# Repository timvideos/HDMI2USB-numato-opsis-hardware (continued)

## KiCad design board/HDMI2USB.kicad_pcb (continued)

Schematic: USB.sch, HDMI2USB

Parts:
C34, C35, C37, C38, C39, C40, C41, C42, C240: 0.1uFD
C43, C44, C52, C53, C54, C58, C66, C201, C202: 0.1MFD
C62, C64: 12pF
D2: LED
GS2: GS2
J1, J7: USB_MICRO_B
P11, P12, P13: CONN_1
P16, P17: CONN_5
P18: CONN_2
R13: 8.06K
R14, R23, R24, R26: 100R
R15, R27, R28: 330R
R30: 20K5%- 0.05W
R31: 1.5K
R32, R35, R36: 10K
R33, R34: 2.2K
R37: 4.7K
U2: CY7C68013A_100AC
U18: USB3340
U24: BDXXGA5WEFJ_
X1: CRYSTAL

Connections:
/FPGA_Bank_1_2/CY-IFCLK: U2.26 (*IFCLK); also elsewhere on the board
/FPGA_Bank_1_2/CYPRESS-RESET: U2.77 (RESET#); also elsewhere on the board
/FPGA_Bank_1_2/CY_CTL0: U2.54 (CTL0/FLAGA); also elsewhere on the board
/FPGA_Bank_1_2/CY_CTL1: U2.55 (CTL1/FLAGB); also elsewhere on the board
/FPGA_Bank_1_2/CY_CTL2: U2.56 (CTL2/FLAGC); also elsewhere on the board
/FPGA_Bank_1_2/CY_CTL3: U2.51 (CTL3); also elsewhere on the board
/FPGA_Bank_1_2/CY_CTL4: U2.52 (CTL4); also elsewhere on the board
/FPGA_Bank_1_2/CY_CTL5: U2.76 (CTL5); also elsewhere on the board
/FPGA_Bank_1_2/CY_FD0: U2.34 (PB0/FD0); also elsewhere on the board
/FPGA_Bank_1_2/CY_FD1: U2.35 (PB1/FD1); also elsewhere on the board
/FPGA_Bank_1_2/CY_FD2: U2.36 (PB2/FD2); also elsewhere on the board
/FPGA_Bank_1_2/CY_FD3: U2.37 (PB3/FD3); also elsewhere on the board
/FPGA_Bank_1_2/CY_FD4: U2.44 (PB4/FD4); also elsewhere on the board
/FPGA_Bank_1_2/CY_FD5: U2.45 (PB5/FD5); also elsewhere on the board
/FPGA_Bank_1_2/CY_FD6: U2.46 (PB6/FD6); also elsewhere on the board
/FPGA_Bank_1_2/CY_FD7: U2.47 (PB7/FD7); also elsewhere on the board
/FPGA_Bank_1_2/CY_FD8: U2.80 (PD0/FD8); also elsewhere on the board
/FPGA_Bank_1_2/CY_FD9: U2.81 (PD1/FD9); also elsewhere on the board
/FPGA_Bank_1_2/CY_FD10: U2.82 (PD2/FD10); also elsewhere on the board
/FPGA_Bank_1_2/CY_FD11: U2.83 (PD3/FD11); also elsewhere on the board
/FPGA_Bank_1_2/CY_FD12: U2.95 (PD4/FD12); also elsewhere on the board
/FPGA_Bank_1_2/CY_FD13: U2.96 (PD5/FD13); also elsewhere on the board
/FPGA_Bank_1_2/CY_FD14: U2.97 (PD6/FD14); also elsewhere on the board
/FPGA_Bank_1_2/CY_FD15: U2.98 (PD7/FD15); also elsewhere on the board
/FPGA_Bank_1_2/CY_INT5: U2.84 (INIT5#); also elsewhere on the board
/FPGA_Bank_1_2/CY_PA0: U2.67 (PA0/INT0#); also elsewhere on the board
/FPGA_Bank_1_2/CY_PA1: U2.68 (PA1/INT1#); also elsewhere on the board
/FPGA_Bank_1_2/CY_PA2: U2.69 (PA2/*SLOE); also elsewhere on the board
/FPGA_Bank_1_2/CY_PA3: U2.70 (PA3/*WU2); also elsewhere on the board
/FPGA_Bank_1_2/CY_PA4: U2.71 (PA4/FIFOADR0); also elsewhere on the board
/FPGA_Bank_1_2/CY_PA5: U2.72 (PA5/FIFOADR1); also elsewhere on the board
/FPGA_Bank_1_2/CY_PA6: U2.73 (PA6/*PKTEND); also elsewhere on the board
/FPGA_Bank_1_2/CY_PA7: U2.74 (PA7/*FLAGD/SLCS#); also elsewhere on the board
/FPGA_Bank_1_2/CY_PC0: U2.57 (PC0/GPIFADR0); also elsewhere on the board
/FPGA_Bank_1_2/CY_PC1: U2.58 (PC1/GPIFADR1); also elsewhere on the board
/FPGA_Bank_1_2/CY_PC2: U2.59 (PC2/GPIFADR2); also elsewhere on the board
/FPGA_Bank_1_2/CY_PC3: U2.60 (PC3/GPIFADR3); also elsewhere on the board
/FPGA_Bank_1_2/CY_PC4: U2.61 (PC4/GPIFADR4); also elsewhere on the board
/FPGA_Bank_1_2/CY_PC5: U2.62 (PC5/GPIFADR5); also elsewhere on the board
/FPGA_Bank_1_2/CY_PC6: U2.63 (PC6/GPIFADR6); also elsewhere on the board
/FPGA_Bank_1_2/CY_PC7: U2.64 (PC7/GPIFADR7); also elsewhere on the board
/FPGA_Bank_1_2/CY_RD: U2.31 (RD#); also elsewhere on the board
/FPGA_Bank_1_2/CY_RD0: U2.3 (RDY0/SLRD); also elsewhere on the board
/FPGA_Bank_1_2/CY_RD1: U2.4 (RDY1/SLWR); also elsewhere on the board
/FPGA_Bank_1_2/CY_RD2: U2.5 (RDY2); also elsewhere on the board
/FPGA_Bank_1_2/CY_RD3: U2.6 (RDY3); also elsewhere on the board
/FPGA_Bank_1_2/CY_RD4: U2.7 (RDY4); also elsewhere on the board
/FPGA_Bank_1_2/CY_RD5: U2.8 (RDY5); also elsewhere on the board
/FPGA_Bank_1_2/CY_RXD0: U2.43 (RXD1); also elsewhere on the board
/FPGA_Bank_1_2/CY_RXD1: U2.41 (RXD0); also elsewhere on the board
/FPGA_Bank_1_2/CY_T0: U2.23 (T0); also elsewhere on the board
/FPGA_Bank_1_2/CY_TXD0: U2.42 (TXD1); also elsewhere on the board
/FPGA_Bank_1_2/CY_TXD1: U2.40 (TXD0); also elsewhere on the board
/FPGA_Bank_1_2/CY_WR: U2.32 (WR#); also elsewhere on the board
/FPGA_Bank_1_2/INIT_B: R27.2; also elsewhere on the board
/FPGA_Bank_1_2/USB_D0: U18.3 (DATA0); also elsewhere on the board
/FPGA_Bank_1_2/USB_D1: U18.4 (DATA1); also elsewhere on the board
/FPGA_Bank_1_2/USB_D2: U18.5 (DATA2); also elsewhere on the board
/FPGA_Bank_1_2/USB_D3: U18.6 (DATA3); also elsewhere on the board
/FPGA_Bank_1_2/USB_D4: U18.7 (DATA4); also elsewhere on the board
/FPGA_Bank_1_2/USB_D5: U18.9 (DATA5); also elsewhere on the board
/FPGA_Bank_1_2/USB_D6: U18.10 (DATA6); also elsewhere on the board
/FPGA_Bank_1_2/USB_D7: U18.13 (DATA7); also elsewhere on the board
/FPGA_Bank_1_2/USB_DIR: U18.31 (DIR); also elsewhere on the board
/FPGA_Bank_1_2/USB_NXT: U18.2 (NXT); also elsewhere on the board
/FPGA_Bank_1_2/USB_REFCLK: U18.26 (REFCLK); also elsewhere on the board
/FPGA_Bank_1_2/USB_RESETB: U18.27 (RESETB); also elsewhere on the board
/FPGA_Bank_1_2/USB_STP: U18.29 (STP); also elsewhere on the board
/FPGA_Power/DONE: R28.2; also elsewhere on the board
/FPGA_Power/PROG_B: R15.2; also elsewhere on the board
/FPGA_Power/TCK: R26.2; also elsewhere on the board
/FPGA_Power/TMS: R24.2; also elsewhere on the board
/SPI_Flash/TDO-FPGA/TDO-JTAG: R14.2; also elsewhere on the board
/SPI_Flash/TDO-USB/TDI-FPGA: R23.2; also elsewhere on the board
/USB/CPEN: U18.17 (CPEN), U24.5 (EN)
/USB/CYDN: J7.2 (D-), P17.2, U2.18 (DMINUS)
/USB/CYDP: J7.3 (D+), P17.3, U2.17 (DPLUS)
/USB/ID: J1.4 (NC), U18.23 (ID)
/USB/U1-SDA: P18.1, R33.1, U2.30 (SDA)
/USB/USB_5V: C240.1, J1.1 (+5V), P16.1, R30.2, U24.1 (VO), U24.2 (FB/VOS)
/USB/USB_DM: J1.2 (D-), P16.2, U18.19 (DM)
/USB/USB_DP: J1.3 (D+), P16.3, U18.18 (DP)
/USB/XTALIN: C62.2, U2.11 (XTALIN), X1.2
/USB/XTALIOUT: C64.1, U2.10 (XTALOUT), X1.1
unnamed: R13.2, U18.24 (RBIAS)
unnamed: C34.1, C35.1, U18.28 (VDD1V8), U18.30 (VDD1V8)
unnamed: R37.1, U2.27 (RESERVED)
unnamed: P11.1, U2.24 (T1)
unnamed: P12.1, U2.25 (T2)
unnamed: P13.1, U2.28 (BKPT)
unnamed: R35.1, U2.79 (*WAKEUP)
unnamed: R14.1, U2.86 (PE0/T0OUT)
unnamed: R23.1, U2.88 (PE2/T2OUT)
unnamed: R24.1, U2.89 (PE3/RXD0OUT)
unnamed: R26.1, U2.90 (PE4/RXD1OUT)
unnamed: R30.1, U18.22 (VBUS)
unnamed: GS2.1 (G1), R32.1, U2.22 (INIT4)
unnamed: R31.1, U2.91 (PE5/INT6)
unnamed: R15.1, U2.87 (PE1/T1OUT)
unnamed: R28.1, U2.93 (PE7/GPIFADR8)
unnamed: R27.1, U2.92 (PE6/T2EX)
unnamed: D2.1 (A), R31.2
unnamed: C37.2, U18.20 (VDD3V3)
unnamed: J7.1 (+5V), P17.1, R36.2
VCC12V0: C38.1, U24.8 (VCC); also elsewhere on the board

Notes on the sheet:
RESET TIMING VALUES
Power-on Reset with crystal
Power-on Reset with external clock
Powered Reset
Condition
RESET
5 ms
200 ∝s + Clock stability time
200 ∝s
24MHz
USB 2.0 OTG Port (Host + Device Support) UTMI+/ULPI IC - Require full FPGA USB2.0 stack Microchip USB3440 FOSS Cores: * Daisho - http://goo.gl/eSwTeb * joris_vr - http://jorisvr.nl/usb/
USB 2.0 Device Port JTAG Programmer and "Easy" High Speed USB 2.0 Interface Cypress FX2 based
Cypress CY7C68013A Decoupling Capacitors
Cypress EEPROM disable

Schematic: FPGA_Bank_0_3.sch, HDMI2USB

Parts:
C113, C191, C192, C193, C194, C195, C196, C197, C198, C199, C200, C245, C246, C247, C248, C249, C250: 0.1UF
R68: 50R
R85: 240E
R120: 4.7K
U10: XC6SLX45T
U27: FXO-LC73
U28, U29: SMA_CON

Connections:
/DDR3/DDR0_A0: U10.K2 (IO_L47P_M3A0_3); also elsewhere on the board
/DDR3/DDR0_A1: U10.K1 (IO_L47N_M3A1_3); also elsewhere on the board
/DDR3/DDR0_A2: U10.K5 (IO_L49N_M3A2_3); also elsewhere on the board
/DDR3/DDR0_A3: U10.M6 (IO_L45P_M3A3_3); also elsewhere on the board
/DDR3/DDR0_A4: U10.H3 (IO_L51N_M3A4_3); also elsewhere on the board
/DDR3/DDR0_A5: U10.M3 (IO_L44P_GCLK21_M3A5_3); also elsewhere on the board
/DDR3/DDR0_A6: U10.L4 (IO_L44N_GCLK20_M3A6_3); also elsewhere on the board
/DDR3/DDR0_A7: U10.K6 (IO_L49P_M3A7_3); also elsewhere on the board
/DDR3/DDR0_A8: U10.G3 (IO_L52P_M3A8_3); also elsewhere on the board
/DDR3/DDR0_A9: U10.G1 (IO_L52N_M3A9_3); also elsewhere on the board
/DDR3/DDR0_A10: U10.J4 (IO_L51P_M3A10_3); also elsewhere on the board
/DDR3/DDR0_A11: U10.E1 (IO_L54N_M3A11_3); also elsewhere on the board
/DDR3/DDR0_A12: U10.F1 (IO_L53N_M3A12_3); also elsewhere on the board
/DDR3/DDR0_A13: U10.J6 (IO_L55P_M3A13_3); also elsewhere on the board
/DDR3/DDR0_A14: U10.H5 (IO_L55N_M3A14_3); also elsewhere on the board
/DDR3/DDR0_BA0: U10.J3 (IO_L48P_M3BA0_3); also elsewhere on the board
/DDR3/DDR0_BA1: U10.J1 (IO_L48N_M3BA1_3); also elsewhere on the board
/DDR3/DDR0_BA2: U10.H1 (IO_L50N_M3BA2_3); also elsewhere on the board
/DDR3/DDR0_CAS_N: U10.M4 (IO_L43N_GCLK22_IRDY2_M3CASN_3); also elsewhere on the board
/DDR3/DDR0_CKE: U10.F2 (IO_L53P_M3CKE_3); also elsewhere on the board
/DDR3/DDR0_CK_N: U10.K3 (IO_L46N_M3CLKN_3); also elsewhere on the board
/DDR3/DDR0_CK_P: U10.K4 (IO_L46P_M3CLK_3); also elsewhere on the board
/DDR3/DDR0_DQ0: U10.R3 (IO_L37P_M3DQ0_3); also elsewhere on the board
/DDR3/DDR0_DQ1: U10.R1 (IO_L37N_M3DQ1_3); also elsewhere on the board
/DDR3/DDR0_DQ2: U10.P2 (IO_L38P_M3DQ2_3); also elsewhere on the board
/DDR3/DDR0_DQ3: U10.P1 (IO_L38N_M3DQ3_3); also elsewhere on the board
/DDR3/DDR0_DQ4: U10.L3 (IO_L41P_GCLK27_M3DQ4_3); also elsewhere on the board
/DDR3/DDR0_DQ5: U10.L1 (IO_L41N_GCLK26_M3DQ5_3); also elsewhere on the board
/DDR3/DDR0_DQ6: U10.M2 (IO_L40P_M3DQ6_3); also elsewhere on the board
/DDR3/DDR0_DQ7: U10.M1 (IO_L40N_M3DQ7_3); also elsewhere on the board
/DDR3/DDR0_DQ8: U10.T2 (IO_L36P_M3DQ8_3); also elsewhere on the board
/DDR3/DDR0_DQ9: U10.T1 (IO_L36N_M3DQ9_3); also elsewhere on the board
/DDR3/DDR0_DQ10: U10.U3 (IO_L35P_M3DQ10_3); also elsewhere on the board
/DDR3/DDR0_DQ11: U10.U1 (IO_L35N_M3DQ11_3); also elsewhere on the board
/DDR3/DDR0_DQ12: U10.W3 (IO_L33P_M3DQ12_3); also elsewhere on the board
/DDR3/DDR0_DQ13: U10.W1 (IO_L33N_M3DQ13_3); also elsewhere on the board
/DDR3/DDR0_DQ14: U10.Y2 (IO_L32P_M3DQ14_3); also elsewhere on the board
/DDR3/DDR0_DQ15: U10.Y1 (IO_L32N_M3DQ15_3); also elsewhere on the board
/DDR3/DDR0_LDM: U10.N4 (IO_L42N_GCLK24_M3LDM_3); also elsewhere on the board
/DDR3/DDR0_LDQS_N: U10.N1 (IO_L39N_M3LDQSN_3); also elsewhere on the board
/DDR3/DDR0_LDQS_P: U10.N3 (IO_L39P_M3LDQS_3); also elsewhere on the board
/DDR3/DDR0_ODT: U10.L6 (IO_L45N_M3ODT_3); also elsewhere on the board
/DDR3/DDR0_RAS_N: U10.M5 (IO_L43P_GCLK23_M3RASN_3); also elsewhere on the board
/DDR3/DDR0_RESET_N: U10.E3 (IO_L54P_M3RESET_3); also elsewhere on the board
/DDR3/DDR0_UDM: U10.P3 (IO_L42P_GCLK25_TRDY2_M3UDM_3); also elsewhere on the board
/DDR3/DDR0_UDQS_N: U10.V1 (IO_L34N_M3UDQSN_3); also elsewhere on the board
/DDR3/DDR0_UDQS_P: U10.V2 (IO_L34P_M3UDQS_3); also elsewhere on the board
/DDR3/DDR0_WE_N: U10.H2 (IO_L50P_M3WE_3); also elsewhere on the board
/DisplayPort/DPRX_LANEN0: U10.C7 (MGTRXN0_101); also elsewhere on the board
/DisplayPort/DPRX_LANEN1: U10.C9 (MGTRXN1_101); also elsewhere on the board
/DisplayPort/DPRX_LANEN2: U10.C13 (*MGTRXN0_123); also elsewhere on the board
/DisplayPort/DPRX_LANEN3: U10.C15 (*MGTRXN1_123); also elsewhere on the board
/DisplayPort/DPRX_LANEP0: U10.D7 (MGTRXP0_101); also elsewhere on the board
/DisplayPort/DPRX_LANEP1: U10.D9 (MGTRXP1_101); also elsewhere on the board
/DisplayPort/DPRX_LANEP2: U10.D13 (*MGTRXP0_123); also elsewhere on the board
/DisplayPort/DPRX_LANEP3: U10.D15 (*MGTRXP1_123); also elsewhere on the board
/DisplayPort/DPTX_LANEN0: U10.A6 (MGTTXN0_101); also elsewhere on the board
/DisplayPort/DPTX_LANEN1: U10.A8 (MGTTXN1_101); also elsewhere on the board
/DisplayPort/DPTX_LANEN2: U10.A14 (*MGTTXN0_123); also elsewhere on the board
/DisplayPort/DPTX_LANEN3: U10.A16 (*MGTTXN1_123); also elsewhere on the board
/DisplayPort/DPTX_LANEP0: U10.B6 (MGTTXP0_101); also elsewhere on the board
/DisplayPort/DPTX_LANEP1: U10.B8 (MGTTXP1_101); also elsewhere on the board
/DisplayPort/DPTX_LANEP2: U10.B14 (*MGTTXP0_123); also elsewhere on the board
/DisplayPort/DPTX_LANEP3: U10.B16 (*MGTTXP1_123); also elsewhere on the board
/Ethernet/MAC_SDA: U10.C1 (IO_L83P_3); also elsewhere on the board
/FPGA_Bank_0_3/DIFFCLK_A0N: U10.F15 (IO_L36N_GCLK14_0); also elsewhere on the board
/FPGA_Bank_0_3/DIFFCLK_A0P: U10.F14 (IO_L36P_GCLK15_0); also elsewhere on the board
/FPGA_Bank_0_3/DIFFCLK_A1N: U10.G9 (IO_L34P_GCLK19_0); also elsewhere on the board
/FPGA_Bank_0_3/DIFFCLK_A1P: U10.F10 (IO_L34N_GCLK18_0); also elsewhere on the board
/FPGA_Bank_0_3/DIFFCLK_B0N: U10.E16 (IO_L37P_GCLK13_0); also elsewhere on the board
/FPGA_Bank_0_3/DIFFCLK_B0P: U10.F16 (IO_L37N_GCLK12_0); also elsewhere on the board
/FPGA_Bank_0_3/DIFFCLK_B1N: U10.G11 (IO_L35N_GCLK16_0); also elsewhere on the board
/FPGA_Bank_0_3/DIFFCLK_B1P: U10.H12 (IO_L35P_GCLK17_0); also elsewhere on the board
/FPGA_Bank_0_3/DIFFCLK_XN: U10.D19 (IO_L62N_VREF_0); also elsewhere on the board
/FPGA_Bank_0_3/DIFFCLK_XP: U10.D18 (IO_L62P_0); also elsewhere on the board
/FPGA_Bank_0_3/DIFFIO_A0N: U10.C18 (IO_L66N_SCP0_0); also elsewhere on the board
/FPGA_Bank_0_3/DIFFIO_A0P: U10.D17 (IO_L66P_SCP1_0); also elsewhere on the board
/FPGA_Bank_0_3/DIFFIO_A1N: U10.A18 (IO_L63N_SCP6_0); also elsewhere on the board
/FPGA_Bank_0_3/DIFFIO_A1P: U10.B18 (IO_L63P_SCP7_0); also elsewhere on the board
/FPGA_Bank_0_3/DIFFIO_A2N: U10.G15 (IO_L49N_0); also elsewhere on the board
/FPGA_Bank_0_3/DIFFIO_A2P: U10.H14 (IO_L49P_0); also elsewhere on the board
/FPGA_Bank_0_3/DIFFIO_A3N: U10.G13 (IO_L38N_VREF_0); also elsewhere on the board
/FPGA_Bank_0_3/DIFFIO_A3P: U10.H13 (IO_L38P_0); also elsewhere on the board
/FPGA_Bank_0_3/DIFFIO_A4N: U10.E6 (IO_L4N_0); also elsewhere on the board
/FPGA_Bank_0_3/DIFFIO_A4P: U10.E5 (IO_L4P_0); also elsewhere on the board
/FPGA_Bank_0_3/DIFFIO_A5N: U10.A4 (IO_L6N_0); also elsewhere on the board
/FPGA_Bank_0_3/DIFFIO_A5P: U10.C4 (IO_L6P_0); also elsewhere on the board
/FPGA_Bank_0_3/DIFFIO_A6N: U10.A2 (IO_L3N_0); also elsewhere on the board
/FPGA_Bank_0_3/DIFFIO_A6P: U10.B2 (IO_L3P_0); also elsewhere on the board
/FPGA_Bank_0_3/DIFFIO_B0N: U10.A20 (IO_L65N_SCP2_0); also elsewhere on the board
/FPGA_Bank_0_3/DIFFIO_B0P: U10.B20 (IO_L65P_SCP3_0); also elsewhere on the board
/FPGA_Bank_0_3/DIFFIO_B1N: U10.F17 (IO_L51N_0); also elsewhere on the board
/FPGA_Bank_0_3/DIFFIO_B1P: U10.G16 (IO_L51P_0); also elsewhere on the board
/FPGA_Bank_0_3/DIFFIO_B2N: U10.A17 (IO_L50N_0); also elsewhere on the board
/FPGA_Bank_0_3/DIFFIO_B2P: U10.C17 (IO_L50P_0); also elsewhere on the board
/FPGA_Bank_0_3/DIFFIO_B3N: U10.H11 (IO_L33N_0); also elsewhere on the board
/FPGA_Bank_0_3/DIFFIO_B3P: U10.H10 (IO_L33P_0); also elsewhere on the board
/FPGA_Bank_0_3/DIFFIO_B4N: U10.D5 (IO_L2N_0); also elsewhere on the board
/FPGA_Bank_0_3/DIFFIO_B4P: U10.D4 (IO_L2P_0); also elsewhere on the board
/FPGA_Bank_0_3/DIFFIO_B5N: U10.A5 (IO_L8N_VREF_0); also elsewhere on the board
/FPGA_Bank_0_3/DIFFIO_B5P: U10.C5 (IO_L8P_0); also elsewhere on the board
/FPGA_Bank_0_3/DIFFIO_B6N: U10.A3 (IO_L5N_0); also elsewhere on the board
/FPGA_Bank_0_3/DIFFIO_B6P: U10.B3 (IO_L5P_0); also elsewhere on the board
/FPGA_Bank_0_3/DIFFIO_XN: U10.A19 (IO_L64N_SCP4_0); also elsewhere on the board
/FPGA_Bank_0_3/DIFFIO_XP: U10.C19 (IO_L64P_SCP5_0); also elsewhere on the board
/FPGA_Bank_0_3/DIFFIO_YN: U10.F8 (IO_L7N_0); also elsewhere on the board
/FPGA_Bank_0_3/DIFFIO_YP: U10.F7 (IO_L7P_0); also elsewhere on the board
/FPGA_Bank_0_3/DIFFIO_ZN: U10.F9 (IO_L32N_0); also elsewhere on the board
/FPGA_Bank_0_3/DIFFIO_ZP: U10.G8 (IO_L32P_0); also elsewhere on the board
/FPGA_Bank_0_3/HSWAP: U10.C3 (IO_L1P_HSWAPEN_0); also elsewhere on the board
/FPGA_Bank_0_3/PCIE_RESET: U10.D3 (IO_L1N_VREF_0); also elsewhere on the board
GTP1V2: C191.1, C193.1, C194.1, C195.1, C196.1, C197.1, C198.1, C199.1, C200.1, R68.1, U10.A7 (MGTAVTTTX_101), U10.A15 (MGTAVTTTX_123), U10.B9 (MGTAVCCPLL0_101), U10.B13 (*MGTAVCCPLL0_123), U10.C10 (MGTAVCC_101), U10.D8 (MGTAVTTRX_101), U10.D12 (MGTAVCCPLL1_101), U10.D14 (MGTAVTTRX_123), U10.E8 (MGTAVTTRCAL_101), U10.E10 (MGTAVCC_123), U10.E13 (*MGTAVCCPLL1_123)
unnamed: R68.2, U10.E9 (MGTRREF_101)
unnamed: R85.2, U10.R7 (IO_L1P_3)
unnamed: C245.2, U10.A10 (MGTREFCLK0P_101)
unnamed: C246.2, U10.B10 (MGTREFCLK0N_101)
unnamed: C247.1, U10.F12 (*MGTREFCLK1N_123)
unnamed: C247.2, U27.5 (OUT_2#)
unnamed: C248.1, U10.E12 (*MGTREFCLK1P_123)
unnamed: C248.2, U27.4 (OUT)
unnamed: C249.1, U10.C11 (MGTREFCLK1P_101)
unnamed: C249.2, U29.2
unnamed: C250.1, U10.D11 (MGTREFCLK1N_101)
unnamed: C250.2, U28.2
unnamed: R120.1, U27.1 (E/D)
unnamed: R120.2, U27.6 (VCC)
VTTREF0: C113.1, C192.1, U10.B1 (IO_L83N_VREF_3), U10.K8 (*IO_L57N_VREF_3), U10.M8 (IO_L31N_VREF_3), U10.P8 (IO_L1N_VREF_3); also elsewhere on the board

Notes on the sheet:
BANK 3
BANK 0

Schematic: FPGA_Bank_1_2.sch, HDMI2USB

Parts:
R54: R
SW1: SW_PUSH
U10: XC6SLX45T

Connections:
/DisplayPort/DPRXAUXCH_N: U10.U10 (*IO_L46N_2); also elsewhere on the board
/DisplayPort/DPRXAUXCH_P: U10.T10 (*IO_L46P_2); also elsewhere on the board
/DisplayPort/DPRXCONFIG1: U10.AA8 (IO_L45P_2); also elsewhere on the board
/DisplayPort/DPRXCONFIG2: U10.AB8 (IO_L45N_2); also elsewhere on the board
/DisplayPort/DPTXAUXCH_N: U10.U15 (*IO_L23N_2); also elsewhere on the board
/DisplayPort/DPTXAUXCH_P: U10.T15 (*IO_L23P_2); also elsewhere on the board
/DisplayPort/DPTXCONFIG1: U10.R11 (*IO_L22P_2); also elsewhere on the board
/DisplayPort/DPTXCONFIG2: U10.T11 (*IO_L22N_2); also elsewhere on the board
/Ethernet/ETH_INT_B: U10.V9 (*IO_L50N_2); also elsewhere on the board
/Ethernet/ETH_MDC: U10.V7 (*IO_L58P_2); also elsewhere on the board
/Ethernet/ETH_MDIO: U10.U8 (*IO_L57N_2); also elsewhere on the board
/Ethernet/ETH_RESET_B: U10.T8 (*IO_L57P_2); also elsewhere on the board
/Ethernet/ETH_RXCLK: U10.AA12 (IO_L31P_GCLK31_D14_2); also elsewhere on the board
/Ethernet/ETH_RXCTL: U10.U9 (*IO_L50P_2); also elsewhere on the board
/Ethernet/ETH_RXD0: U10.R9 (*IO_L59P_2); also elsewhere on the board
/Ethernet/ETH_RXD1: U10.R8 (*IO_L59N_2); also elsewhere on the board
/Ethernet/ETH_RXD2: U10.W6 (*IO_L60P_2); also elsewhere on the board
/Ethernet/ETH_RXD3: U10.Y6 (*IO_L60N_2); also elsewhere on the board
/Ethernet/ETH_TXCLK: U10.AB12 (IO_L31N_GCLK30_D15_2); also elsewhere on the board
/Ethernet/ETH_TXCTL: U10.W8 (*IO_L58N_2); also elsewhere on the board
/Ethernet/ETH_TXD0: U10.W9 (IO_L48P_D7_2); also elsewhere on the board
/Ethernet/ETH_TXD1: U10.Y8 (IO_L48N_RDWR_B_VREF_2); also elsewhere on the board
/Ethernet/ETH_TXD2: U10.AA6 (IO_L49P_D3_2); also elsewhere on the board
/Ethernet/ETH_TXD3: U10.AB6 (IO_L49N_D4_2); also elsewhere on the board
/FPGA_Bank_1_2/CY-IFCLK: U10.P20 (IO_L42P_GCLK7_M1UDM_1); also elsewhere on the board
/FPGA_Bank_1_2/CYPRESS-RESET: U10.G22 (IO_L35N_A10_M1A2_1); also elsewhere on the board
/FPGA_Bank_1_2/CY_CTL0: U10.N16 (IO_L60P_1); also elsewhere on the board
/FPGA_Bank_1_2/CY_CTL1: U10.P16 (IO_L60N_1); also elsewhere on the board
/FPGA_Bank_1_2/CY_CTL2: U10.R15 (*IO_L70P_1); also elsewhere on the board
/FPGA_Bank_1_2/CY_CTL3: U10.M18 (IO_L61N_1); also elsewhere on the board
/FPGA_Bank_1_2/CY_CTL4: U10.M17 (IO_L61P_1); also elsewhere on the board
/FPGA_Bank_1_2/CY_CTL5: U10.R16 (*IO_L70N_1); also elsewhere on the board
/FPGA_Bank_1_2/CY_FD0: U10.C20 (IO_L20P_1); also elsewhere on the board
/FPGA_Bank_1_2/CY_FD1: U10.C22 (IO_L20N_1); also elsewhere on the board
/FPGA_Bank_1_2/CY_FD2: U10.L15 (*IO_L21P_1); also elsewhere on the board
/FPGA_Bank_1_2/CY_FD3: U10.K16 (*IO_L21N_1); also elsewhere on the board
/FPGA_Bank_1_2/CY_FD4: U10.D21 (*IO_L28P_1); also elsewhere on the board
/FPGA_Bank_1_2/CY_FD5: U10.D22 (*IO_L28N_VREF_1); also elsewhere on the board
/FPGA_Bank_1_2/CY_FD6: U10.G19 (IO_L29P_A23_M1A13_1); also elsewhere on the board
/FPGA_Bank_1_2/CY_FD7: U10.F20 (IO_L29N_A22_M1A14_1); also elsewhere on the board
/FPGA_Bank_1_2/CY_FD8: U10.H18 (IO_L30P_A21_M1RESET_1); also elsewhere on the board
/FPGA_Bank_1_2/CY_FD9: U10.H19 (IO_L30N_A20_M1A11_1); also elsewhere on the board
/FPGA_Bank_1_2/CY_FD10: U10.F21 (IO_L31P_A19_M1CKE_1); also elsewhere on the board
/FPGA_Bank_1_2/CY_FD11: U10.F22 (IO_L31N_A18_M1A12_1); also elsewhere on the board
/FPGA_Bank_1_2/CY_FD12: U10.E20 (IO_L32P_A17_M1A8_1); also elsewhere on the board
/FPGA_Bank_1_2/CY_FD13: U10.E22 (IO_L32N_A16_M1A9_1); also elsewhere on the board
/FPGA_Bank_1_2/CY_FD14: U10.J19 (IO_L33P_A15_M1A10_1); also elsewhere on the board
/FPGA_Bank_1_2/CY_FD15: U10.H20 (IO_L33N_A14_M1A4_1); also elsewhere on the board
/FPGA_Bank_1_2/CY_INT5: U10.T19 (*IO_L73P_1); also elsewhere on the board
/FPGA_Bank_1_2/CY_PA0: U10.F18 (IO_L1P_A25_1); also elsewhere on the board
/FPGA_Bank_1_2/CY_PA1: U10.F19 (IO_L1N_A24_VREF_1); also elsewhere on the board
/FPGA_Bank_1_2/CY_PA2: U10.H16 (*IO_L9P_1); also elsewhere on the board
/FPGA_Bank_1_2/CY_PA3: U10.H17 (*IO_L9N_1); also elsewhere on the board
/FPGA_Bank_1_2/CY_PA4: U10.B21 (*IO_L10P_1); also elsewhere on the board
/FPGA_Bank_1_2/CY_PA5: U10.B22 (*IO_L10N_1); also elsewhere on the board
/FPGA_Bank_1_2/CY_PA6: U10.J16 (IO_L19P_1); also elsewhere on the board
/FPGA_Bank_1_2/CY_PA7: U10.J17 (IO_L19N_1); also elsewhere on the board
/FPGA_Bank_1_2/CY_PC0: U10.U20 (IO_L49P_M1DQ10_1); also elsewhere on the board
/FPGA_Bank_1_2/CY_PC1: U10.U22 (IO_L49N_M1DQ11_1); also elsewhere on the board
/FPGA_Bank_1_2/CY_PC2: U10.V21 (IO_L50P_M1UDQS_1); also elsewhere on the board
/FPGA_Bank_1_2/CY_PC3: U10.V22 (IO_L50N_M1UDQSN_1); also elsewhere on the board
/FPGA_Bank_1_2/CY_PC4: U10.W20 (IO_L51P_M1DQ12_1); also elsewhere on the board
/FPGA_Bank_1_2/CY_PC5: U10.W22 (IO_L51N_M1DQ13_1); also elsewhere on the board
/FPGA_Bank_1_2/CY_PC6: U10.Y21 (IO_L52P_M1DQ14_1); also elsewhere on the board
/FPGA_Bank_1_2/CY_PC7: U10.Y22 (IO_L52N_M1DQ15_1); also elsewhere on the board
/FPGA_Bank_1_2/CY_RD: U10.K19 (IO_L34P_A13_M1WE_1); also elsewhere on the board
/FPGA_Bank_1_2/CY_RD0: U10.P19 (IO_L53P_1); also elsewhere on the board
/FPGA_Bank_1_2/CY_RD1: U10.R19 (IO_L53N_VREF_1); also elsewhere on the board
/FPGA_Bank_1_2/CY_RD2: U10.M16 (*IO_L58P_1); also elsewhere on the board
/FPGA_Bank_1_2/CY_RD3: U10.N15 (*IO_L58N_1); also elsewhere on the board
/FPGA_Bank_1_2/CY_RD4: U10.U19 (IO_L59P_1); also elsewhere on the board
/FPGA_Bank_1_2/CY_RD5: U10.T20 (IO_L59N_1); also elsewhere on the board
/FPGA_Bank_1_2/CY_RXD0: U10.P17 (*IO_L71P_1); also elsewhere on the board
/FPGA_Bank_1_2/CY_RXD1: U10.P18 (*IO_L71N_1); also elsewhere on the board
/FPGA_Bank_1_2/CY_T0: U10.G20 (IO_L35P_A11_M1A7_1); also elsewhere on the board
/FPGA_Bank_1_2/CY_TXD0: U10.R17 (*IO_L72P_1); also elsewhere on the board
/FPGA_Bank_1_2/CY_TXD1: U10.T17 (*IO_L72N_1); also elsewhere on the board
/FPGA_Bank_1_2/CY_WR: U10.K18 (IO_L34N_A12_M1BA2_1); also elsewhere on the board
/FPGA_Bank_1_2/DPRXHPD: U10.W11 (*IO_L42N_2); also elsewhere on the board
/FPGA_Bank_1_2/DPTXHPD: U10.V11 (*IO_L42P_2); also elsewhere on the board
/FPGA_Bank_1_2/FPGA_M0_CMP_MISO: U10.AA21 (IO_L1N_M0_CMPMISO_2); also elsewhere on the board
/FPGA_Bank_1_2/FPGA_M1: U10.Y19 (IO_L13P_M1_2); also elsewhere on the board
/FPGA_Bank_1_2/INIT_B: U10.Y4 (IO_L65P_INIT_B_2); also elsewhere on the board
/FPGA_Bank_1_2/SD_CLK: U10.U6 (IO_L64N_D9_2); also elsewhere on the board
/FPGA_Bank_1_2/SD_CMD: U10.T7 (IO_L64P_D8_2); also elsewhere on the board
/FPGA_Bank_1_2/SD_DAT0: U10.Y5 (IO_L62P_D5_2); also elsewhere on the board
/FPGA_Bank_1_2/SD_DAT1: U10.AB5 (IO_L62N_D6_2); also elsewhere on the board
/FPGA_Bank_1_2/SD_DAT2: U10.AB4 (IO_L63N_2); also elsewhere on the board
/FPGA_Bank_1_2/SD_DAT3: U10.AA4 (IO_L63P_2); also elsewhere on the board
/FPGA_Bank_1_2/SPI_CLK: U10.Y20 (IO_L1P_CCLK_2); also elsewhere on the board
/FPGA_Bank_1_2/SPI_CS_N: U10.AA3 (IO_L65N_CSO_B_2); also elsewhere on the board
/FPGA_Bank_1_2/SPI_D1_MISO2: U10.R13 (IO_L12P_D1_MISO2_2); also elsewhere on the board
/FPGA_Bank_1_2/SPI_D2_MISO3: U10.T14 (IO_L12N_D2_MISO3_2); also elsewhere on the board
/FPGA_Bank_1_2/SPI_DO_DIN_MISO1: U10.AA20 (IO_L3P_D0_DIN_MISO_MISO1_2); also elsewhere on the board
/FPGA_Bank_1_2/SPI_MOSI_CSI_N_MISO0: U10.AB20 (IO_L3N_MOSI_CSI_B_MISO0_2); also elsewhere on the board
/FPGA_Bank_1_2/SWITCH: R54.1, U10.AB19 (IO_L13N_D10_2)
/FPGA_Bank_1_2/USB_D0: U10.U16 (*IO_L4P_2); also elsewhere on the board
/FPGA_Bank_1_2/USB_D1: U10.V15 (*IO_L4N_VREF_2); also elsewhere on the board
/FPGA_Bank_1_2/USB_D2: U10.W17 (*IO_L5P_2); also elsewhere on the board
/FPGA_Bank_1_2/USB_D3: U10.Y18 (*IO_L5N_2); also elsewhere on the board
/FPGA_Bank_1_2/USB_D4: U10.AA14 (IO_L6P_2); also elsewhere on the board
/FPGA_Bank_1_2/USB_D5: U10.AB14 (IO_L6N_2); also elsewhere on the board
/FPGA_Bank_1_2/USB_D6: U10.Y16 (*IO_L17P_2); also elsewhere on the board
/FPGA_Bank_1_2/USB_D7: U10.W15 (*IO_L17N_2); also elsewhere on the board
/FPGA_Bank_1_2/USB_DIR: U10.W13 (*IO_L18N_2); also elsewhere on the board
/FPGA_Bank_1_2/USB_NXT: U10.V13 (*IO_L18P_2); also elsewhere on the board
/FPGA_Bank_1_2/USB_REFCLK: U10.Y13 (IO_L30P_GCLK1_D13_2); also elsewhere on the board
/FPGA_Bank_1_2/USB_RESETB: U10.V17 (IO_L2P_CMPCLK_2); also elsewhere on the board
/FPGA_Bank_1_2/USB_STP: U10.W18 (IO_L2N_CMPMOSI_2); also elsewhere on the board
/FPGA_Bank_1_2/USRCLK: U10.AB13 (IO_L30N_GCLK0_USERCCLK_2); also elsewhere on the board
/HDMI/TMDS-RX1-0_N: U10.J22 (IO_L39N_M1ODT_1); also elsewhere on the board
/HDMI/TMDS-RX1-0_P: U10.J20 (IO_L39P_M1A3_1); also elsewhere on the board
/HDMI/TMDS-RX1-1_N: U10.L19 (IO_L38N_A4_M1CLKN_1); also elsewhere on the board
/HDMI/TMDS-RX1-1_P: U10.K20 (IO_L38P_A5_M1CLK_1); also elsewhere on the board
/HDMI/TMDS-RX1-2_N: U10.H22 (IO_L37N_A6_M1A1_1); also elsewhere on the board
/HDMI/TMDS-RX1-2_P: U10.H21 (IO_L37P_A7_M1A0_1); also elsewhere on the board
/HDMI/TMDS-RX1-CEC: U10.K17 (IO_L36P_A9_M1BA0_1); also elsewhere on the board
/HDMI/TMDS-RX1-CLK_N: U10.M19 (IO_L40N_GCLK10_M1A6_1); also elsewhere on the board
/HDMI/TMDS-RX1-CLK_P: U10.M20 (IO_L40P_GCLK11_M1A5_1); also elsewhere on the board
/HDMI/TMDS-RX1-HOT: U10.V19 (IO_L74P_AWAKE_1); also elsewhere on the board
/HDMI/TMDS-RX1-SCL: U10.L17 (IO_L36N_A8_M1BA1_1); also elsewhere on the board
/HDMI/TMDS-RX1-SDA: U10.T18 (*IO_L73N_1); also elsewhere on the board
/HDMI/TMDS-RX2-0_N: U10.M22 (IO_L44N_A2_M1DQ7_1); also elsewhere on the board
/HDMI/TMDS-RX2-0_P: U10.M21 (IO_L44P_A3_M1DQ6_1); also elsewhere on the board
/HDMI/TMDS-RX2-1_N: U10.N22 (IO_L45N_A0_M1LDQSN_1); also elsewhere on the board
/HDMI/TMDS-RX2-1_P: U10.N20 (IO_L45P_A1_M1LDQS_1); also elsewhere on the board
/HDMI/TMDS-RX2-2_N: U10.P22 (IO_L46N_FOE_B_M1DQ3_1); also elsewhere on the board
/HDMI/TMDS-RX2-2_P: U10.P21 (IO_L46P_FCS_B_M1DQ2_1); also elsewhere on the board
/HDMI/TMDS-RX2-CEC: U10.T21 (IO_L48P_HDC_M1DQ8_1); also elsewhere on the board
/HDMI/TMDS-RX2-CLK_N: U10.L22 (IO_L43N_GCLK4_M1DQ5_1); also elsewhere on the board
/HDMI/TMDS-RX2-CLK_P: U10.L20 (IO_L43P_GCLK5_M1DQ4_1); also elsewhere on the board
/HDMI/TMDS-RX2-HOT: U10.T22 (IO_L48N_M1DQ9_1); also elsewhere on the board
/HDMI/TMDS-RX2-SCL: U10.R20 (IO_L47P_FWE_B_M1DQ0_1); also elsewhere on the board
/HDMI/TMDS-RX2-SDA: U10.R22 (IO_L47N_LDC_M1DQ1_1); also elsewhere on the board
/HDMI/TMDS-TX1-0_N: U10.Y12 (IO_L40N_2); also elsewhere on the board
/HDMI/TMDS-TX1-0_P: U10.W12 (IO_L40P_2); also elsewhere on the board
/HDMI/TMDS-TX1-1_N: U10.AB10 (IO_L41N_VREF_2); also elsewhere on the board
/HDMI/TMDS-TX1-1_P: U10.AA10 (IO_L41P_2); also elsewhere on the board
/HDMI/TMDS-TX1-2_N: U10.AB9 (IO_L43N_2); also elsewhere on the board
/HDMI/TMDS-TX1-2_P: U10.Y9 (IO_L43P_2); also elsewhere on the board
/HDMI/TMDS-TX1-CEC: U10.Y7 (IO_L47P_2); also elsewhere on the board
/HDMI/TMDS-TX1-CLK_N: U10.AB11 (IO_L32N_GCLK28_2); also elsewhere on the board
/HDMI/TMDS-TX1-CLK_P: U10.Y11 (IO_L32P_GCLK29_2); also elsewhere on the board
/HDMI/TMDS-TX1-HOT: U10.AB7 (IO_L47N_2); also elsewhere on the board
/HDMI/TMDS-TX1-SCL: U10.W10 (*IO_L44P_2); also elsewhere on the board
/HDMI/TMDS-TX1-SDA: U10.Y10 (*IO_L44N_2); also elsewhere on the board
/HDMI/TMDS-TX2-0_N: U10.AB15 (IO_L21N_2); also elsewhere on the board
/HDMI/TMDS-TX2-0_P: U10.Y15 (IO_L21P_2); also elsewhere on the board
/HDMI/TMDS-TX2-1_N: U10.AB16 (IO_L19N_2); also elsewhere on the board
/HDMI/TMDS-TX2-1_P: U10.AA16 (IO_L19P_2); also elsewhere on the board
/HDMI/TMDS-TX2-2_N: U10.U13 (IO_L16N_VREF_2); also elsewhere on the board
/HDMI/TMDS-TX2-2_P: U10.U14 (IO_L16P_2); also elsewhere on the board
/HDMI/TMDS-TX2-CEC: U10.AA18 (IO_L14P_D11_2); also elsewhere on the board
/HDMI/TMDS-TX2-CLK_N: U10.U12 (IO_L29N_GCLK2_2); also elsewhere on the board
/HDMI/TMDS-TX2-CLK_P: U10.T12 (IO_L29P_GCLK3_2); also elsewhere on the board
/HDMI/TMDS-TX2-HOT: U10.AB18 (IO_L14N_D12_2); also elsewhere on the board
/HDMI/TMDS-TX2-SCL: U10.Y17 (IO_L15P_2); also elsewhere on the board
/HDMI/TMDS-TX2-SDA: U10.AB17 (IO_L15N_2); also elsewhere on the board
unnamed: R54.2, SW1.1

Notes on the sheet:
BANK 2
BANK 1

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
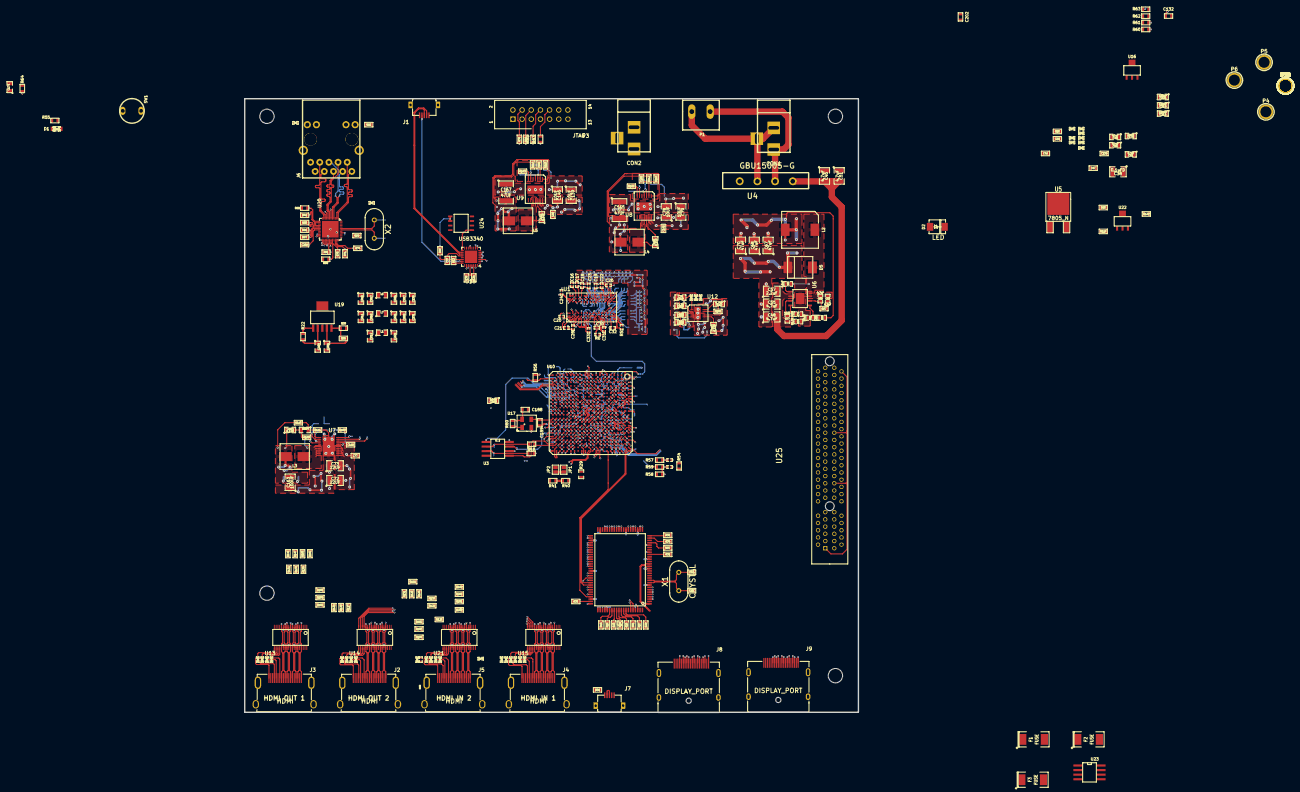
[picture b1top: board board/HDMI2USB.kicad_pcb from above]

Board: 10 copper layers, 170.0 x 170.0 mm, 466 parts (0 on the bottom side), 426 nets.

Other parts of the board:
1PIN, 1PIN#2, 1PIN#3, 1PIN#4: P***; MH-4MM

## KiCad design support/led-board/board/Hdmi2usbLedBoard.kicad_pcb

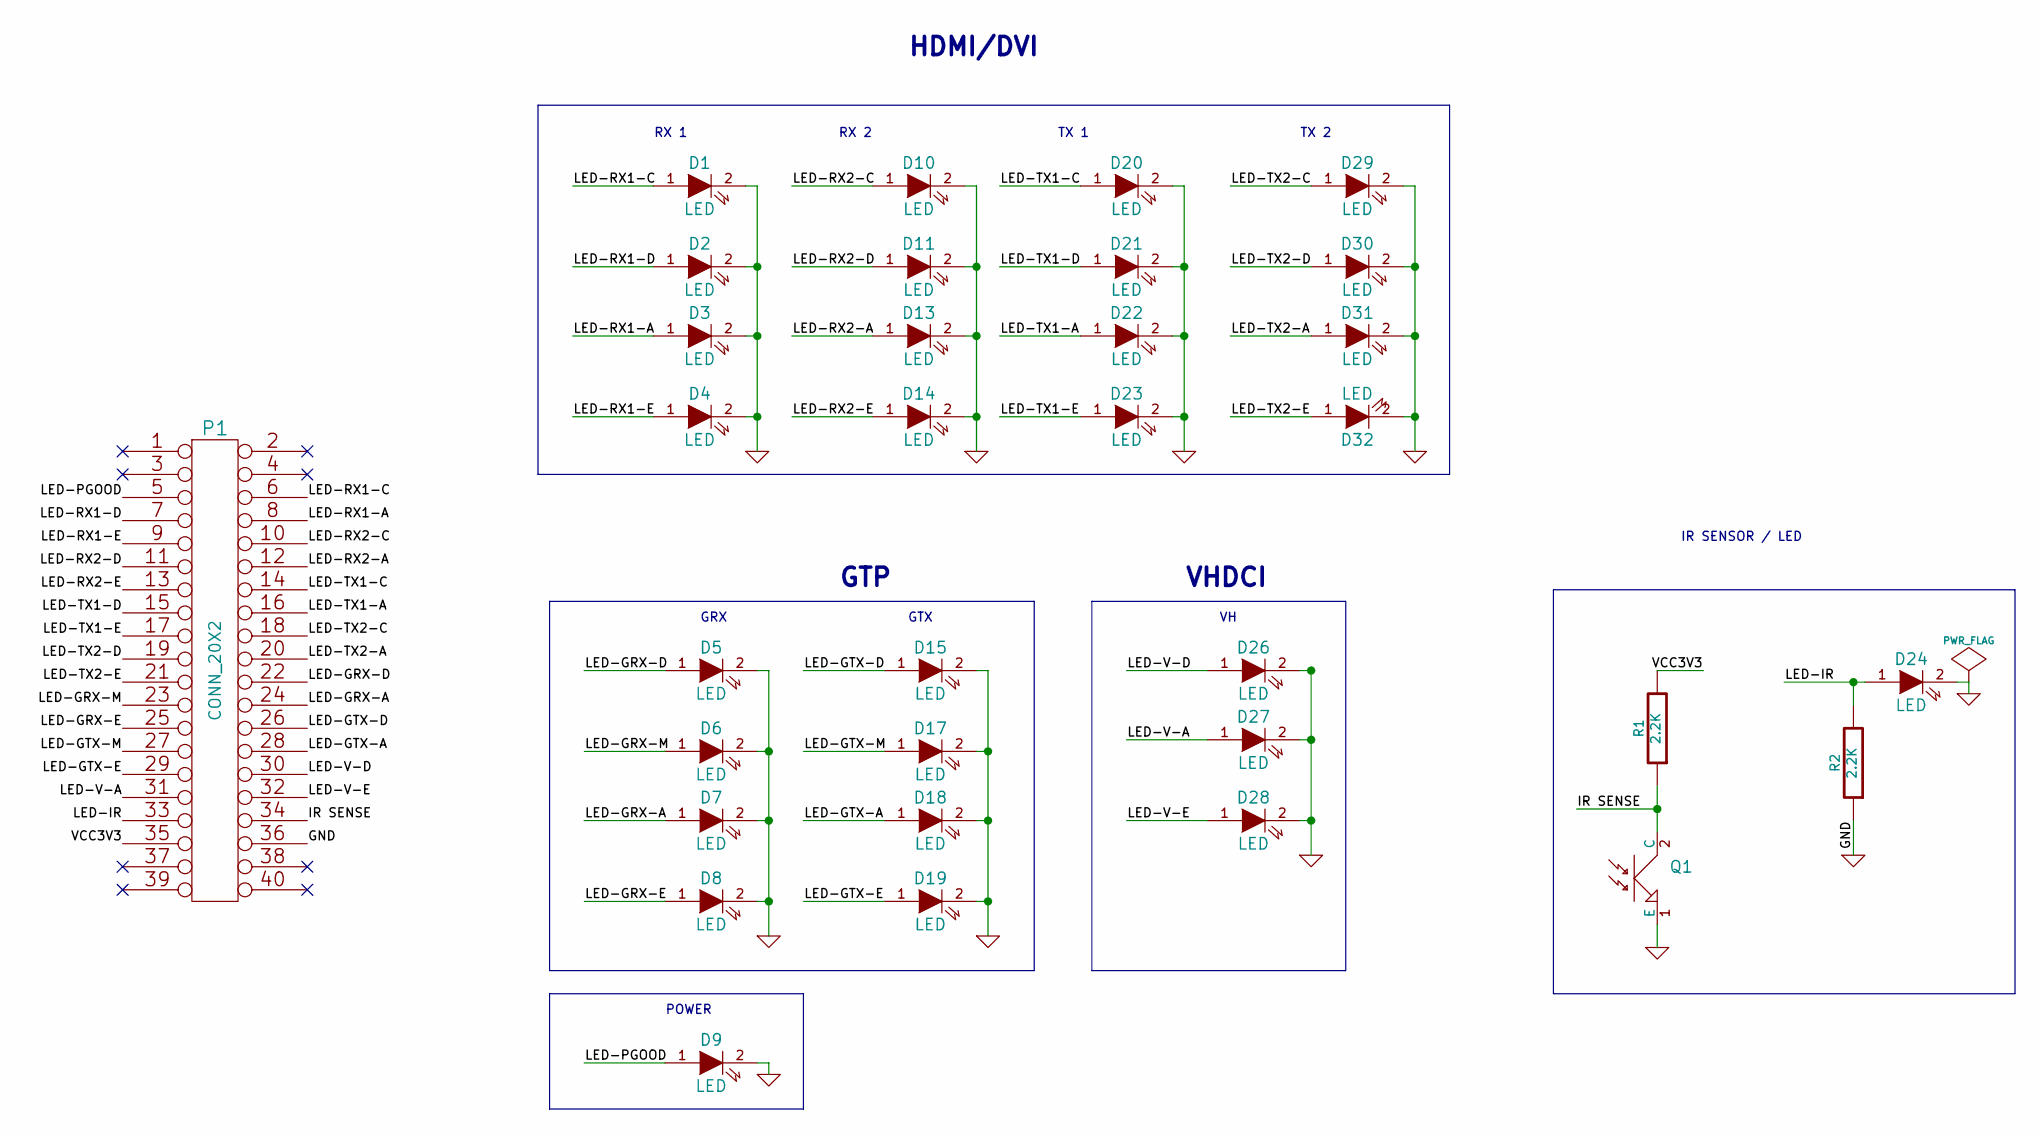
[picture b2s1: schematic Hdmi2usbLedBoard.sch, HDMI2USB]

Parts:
D1, D2, D3, D4, D5, D6, D7, D8, D9, D10, D11, D13, D14, D15, D17, D18, D19, D20, D21, D22, D23, D24, D26, D27, D28, D29, D30, D31, D32: LED
P1: CONN_20X2
Q1: OPTO_NPN
R1, R2: 2.2K

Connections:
/IR SENSE: P1.34, Q1.2 (C), R1.1
/LED-GRX-A: D7.1 (A), P1.24
/LED-GRX-D: D5.1 (A), P1.22
/LED-GRX-E: D8.1 (A), P1.25
/LED-GRX-M: D6.1 (A), P1.23
/LED-GTX-A: D18.1 (A), P1.28
/LED-GTX-D: D15.1 (A), P1.26
/LED-GTX-E: D19.1 (A), P1.29
/LED-GTX-M: D17.1 (A), P1.27
/LED-IR: D24.1 (A), P1.33, R2.2
/LED-PGOOD: D9.1 (A), P1.5
/LED-RX1-A: D3.1 (A), P1.8
/LED-RX1-C: D1.1 (A), P1.6
/LED-RX1-D: D2.1 (A), P1.7
/LED-RX1-E: D4.1 (A), P1.9
/LED-RX2-A: D13.1 (A), P1.12
/LED-RX2-C: D10.1 (A), P1.10
/LED-RX2-D: D11.1 (A), P1.11
/LED-RX2-E: D14.1 (A), P1.13
/LED-TX1-A: D22.1 (A), P1.16
/LED-TX1-C: D20.1 (A), P1.14
/LED-TX1-D: D21.1 (A), P1.15
/LED-TX1-E: D23.1 (A), P1.17
/LED-TX2-A: D31.1 (A), P1.20
/LED-TX2-C: D29.1 (A), P1.18
/LED-TX2-D: D30.1 (A), P1.19
/LED-TX2-E: D32.1 (A), P1.21
/LED-V-A: D27.1 (A), P1.31
/LED-V-D: D26.1 (A), P1.30
/LED-V-E: D28.1 (A), P1.32
/VCC3V3: P1.35, R1.2
GND: D1.2 (K), D2.2 (K), D3.2 (K), D4.2 (K), D5.2 (K), D6.2 (K), D7.2 (K), D8.2 (K), D9.2 (K), D10.2 (K), D11.2 (K), D13.2 (K), D14.2 (K), D15.2 (K), D17.2 (K), D18.2 (K), D19.2 (K), D20.2 (K), D21.2 (K), D22.2 (K), D23.2 (K), D24.2 (K), D26.2 (K), D27.2 (K), D28.2 (K), D29.2 (K), D30.2 (K), D31.2 (K), D32.2 (K), P1.36, Q1.1 (E), R2.1; also elsewhere on the board

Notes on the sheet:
RX 1
RX 2
TX 1
TX 2
HDMI/DVI
GRX
GTX
VHDCI
POWER
IR SENSOR / LED
GTP

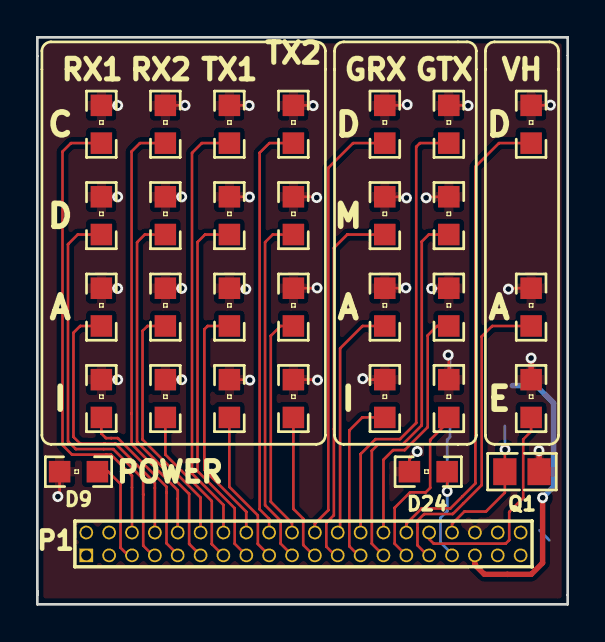
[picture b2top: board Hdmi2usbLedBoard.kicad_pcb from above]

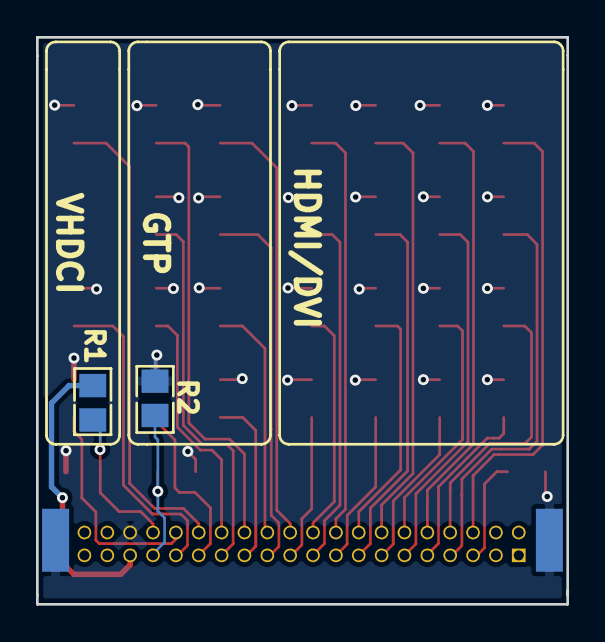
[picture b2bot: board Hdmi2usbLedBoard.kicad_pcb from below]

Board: 2 copper layers, 29.5 x 31.5 mm, 35 parts (4 on the bottom side), 32 nets.

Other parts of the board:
1PIN, 1PIN#2: P***; MH-3.2MM

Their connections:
GND: 1PIN.0, 1PIN#2.0; also elsewhere on the board
